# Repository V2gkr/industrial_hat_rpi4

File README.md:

HAT for Raspberry PI 4 with isolated rs232 , rs485 , CAN-FD

This board was made for personal use with other projects.
outputs for manufacturing:
1) gerbers and drill files
2) BOM for jlcpcb store
3) pick and place file

Board capabilities
1) isolated RS232 on standart UART pins (8 , 10)
2) isolated RS485 on additional UART with enable pin (27,28,29)
3) isolated CAN-FD on SPI0 (standard pins with interrupt pin on pin 15)

Production cost on jlcpcb for 5 prototypes is app. 150$

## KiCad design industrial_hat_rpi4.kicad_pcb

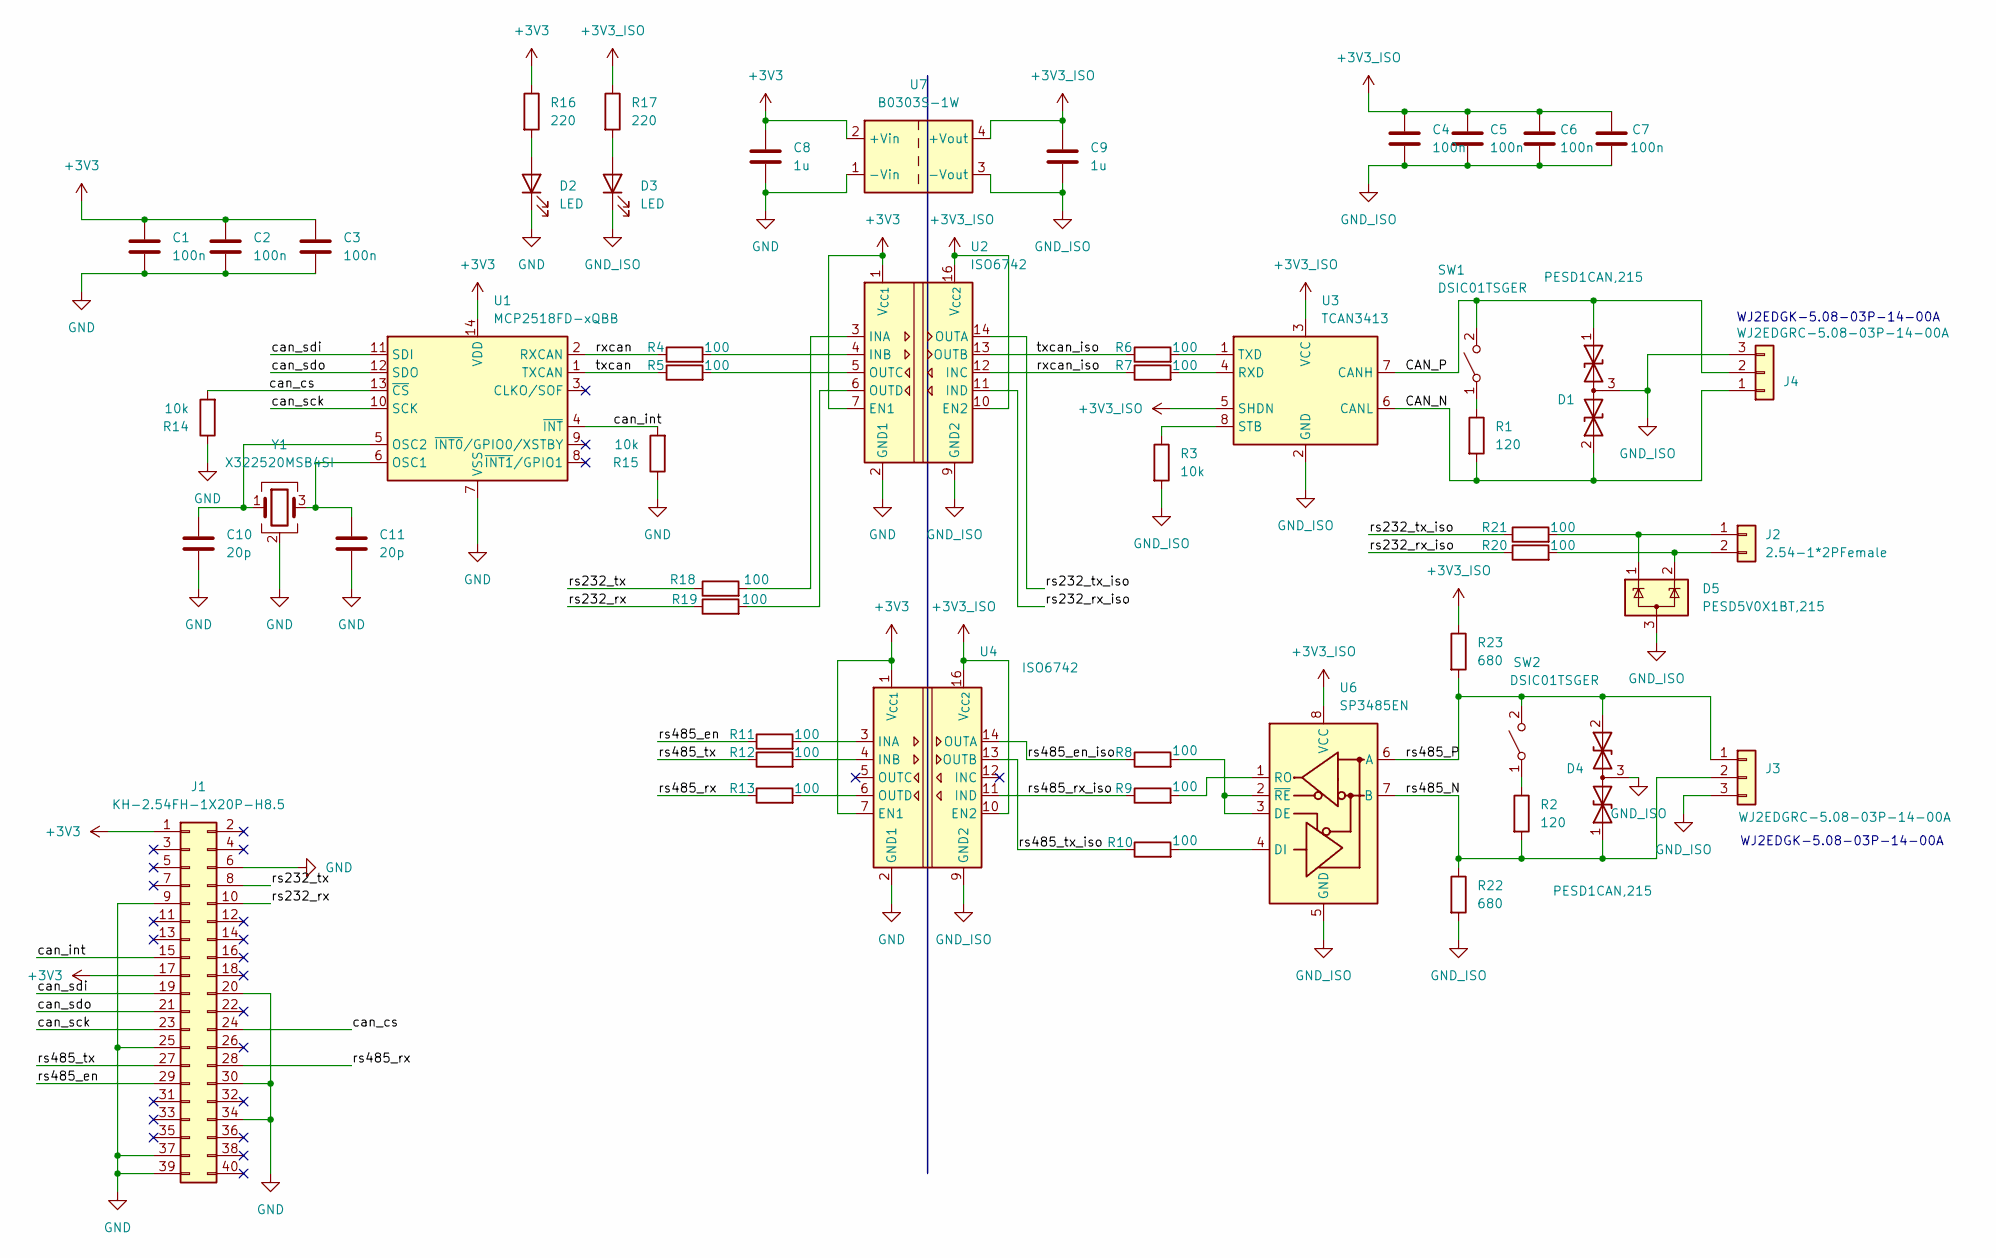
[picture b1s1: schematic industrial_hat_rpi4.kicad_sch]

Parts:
C1, C2, C3, C4, C5, C6, C7: 100n; C_0402_1005Metric; LCSC C60474
C8, C9: 1u; C_0603_1608Metric; LCSC C3905328
C10, C11: 20p; C_0402_1005Metric; LCSC C76959
D1, D4: PESD1CAN,215; SOT-23; LCSC C15771
D2, D3: LED; LED_0603_1608Metric; LCSC C99289
D5: PESD5V0X1BT,215; SOT-23-3; LCSC C456094
J1: KH-2.54FH-1X20P-H8.5; PinSocket_2x20_P2.54mm_Vertical_jlcbpcb_pnp_custom; LCSC C2905423
J2: 2.54-1*2PFemale; PinSocket_1x02_P2.54mm_Vertical_jlcpcb_pnp_custom; LCSC C49661
J3, J4: WJ2EDGRC-5.08-03P-14-00A; PhoenixContact_MSTBA_2,5_3-G-5,08_1x03_P5.08mm_Horizontal; LCSC C8377
R1, R2: 120; R_0603_1608Metric; LCSC C114681
R3, R14, R15: 10k; R_0603_1608Metric; LCSC C22369937
R4, R5, R6, R7, R8, R9, R10, R11, R12, R13, R18, R19, R20, R21: 100; R_0603_1608Metric; LCSC C163844
R16, R17: 220; R_0603_1608Metric; LCSC C384263
R22, R23: 680; R_0603_1608Metric; LCSC C25253
SW1, SW2: DSIC01TSGER; SW_DIP_SPSTx01_Slide_Copal_CHS-01B_W7.62mm_P1.27mm; LCSC C5145031
U1: MCP2518FD-xQBB; DFN-14-1EP_3x4.5mm_P0.65mm_EP1.65x4.25mm; LCSC C621395
U2, U4: ISO6742; SOIC-16W_7.5x10.3mm_P1.27mm; LCSC C5216407
U3: TCAN3413; SOIC-8_3.9x4.9mm_P1.27mm; LCSC C22433320
U6: SP3485EN; SOIC-8_3.9x4.9mm_P1.27mm; LCSC C22386564
U7: B0303S-1W; Converter_DCDC_Murata_CRE1xxxxxxSC_THT_jlcpcb_pnp_custom; LCSC C20622556
Y1: X322520MSB4SI; Crystal_SMD_3225-4Pin_3.2x2.5mm; LCSC C9004

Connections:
+3V3: C1.1, C2.1, C3.1, C8.1, J1.1, J1.17, R16.1, U1.14 (VDD), U2.1 (V_{CC1}), U2.7 (EN1), U4.1 (V_{CC1}), U4.7 (EN1), U7.2 (+Vin)
+3V3_ISO: C4.1, C5.1, C6.1, C7.1, C9.1, R17.1, R23.1, U2.10 (EN2), U2.16 (V_{CC2}), U3.3 (VCC), U3.5 (SHDN), U4.10 (EN2), U4.16 (V_{CC2}), U6.8 (VCC), U7.4 (+Vout)
/CAN_N: D1.2 (A2), J4.1, R1.2, U3.6 (CANL)
/CAN_P: D1.1 (A1), J4.2, SW1.2 (B), U3.7 (CANH)
/can_cs: J1.24, R14.2, U1.13 (~CS)
/can_int: J1.15, R15.2, U1.4 (~INT)
/can_sck: J1.23, U1.10 (SCK)
/can_sdi: J1.19, U1.11 (SDI)
/can_sdo: J1.21, U1.12 (SDO)
/rs232_rx: J1.10, R19.1
/rs232_rx_iso: R20.1, U2.11 (IND)
/rs232_tx: J1.8, R18.1
/rs232_tx_iso: R21.1, U2.14 (OUTA)
/rs485_N: D4.1 (A1), J3.2, R2.2, R22.1, U6.7 (B)
/rs485_P: D4.2 (A2), J3.1, R23.2, SW2.2 (B), U6.6 (A)
/rs485_en: J1.29, R11.1
/rs485_en_iso: R8.1, U4.14 (OUTA)
/rs485_rx: J1.28, R13.1
/rs485_rx_iso: R9.1, U4.11 (IND)
/rs485_tx: J1.27, R12.1
/rs485_tx_iso: R10.1, U4.13 (OUTB)
/rxcan: R4.1, U1.2 (RXCAN)
/rxcan_iso: R7.1, U2.12 (INC)
/txcan: R5.1, U1.1 (TXCAN)
/txcan_iso: R6.1, U2.13 (OUTB)
GND: C1.2, C2.2, C3.2, C8.2, C10.2, C11.2, D2.1 (K), J1.6, J1.9, J1.20, J1.25, J1.30, J1.34, J1.37, J1.39, R14.1, R15.1, U1.7 (VSS), U1.15 (VSS), U2.2 (GND1), U2.8 (GND1), U4.2 (GND1), U4.8 (GND1), U7.1 (-Vin), Y1.2 (G), Y1.4 (G)
GND_ISO: C4.2, C5.2, C6.2, C7.2, C9.2, D1.3 (common), D3.1 (K), D4.3 (common), D5.3 (A), J3.3, J4.3, R3.2, R22.2, U2.9 (GND2), U2.15 (GND2), U3.2 (GND), U4.9 (GND2), U4.15 (GND2), U6.5 (GND), U7.3 (-Vout)
unnamed: D2.2 (A), R16.2
unnamed: D3.2 (A), R17.2
unnamed: D5.1 (K), J2.1, R21.2
unnamed: D5.2 (K), J2.2, R20.2
unnamed: R1.1, SW1.1 (A)
unnamed: R2.1, SW2.1 (A)
unnamed: C11.1, U1.6 (OSC1), Y1.3
unnamed: C10.1, U1.5 (OSC2), Y1.1
unnamed: R18.2, U2.3 (INA)
unnamed: R4.2, U2.4 (INB)
unnamed: R5.2, U2.5 (OUTC)
unnamed: R19.2, U2.6 (OUTD)
unnamed: R7.2, U3.4 (RXD)
unnamed: R3.1, U3.8 (STB)
unnamed: R6.2, U3.1 (TXD)
unnamed: R11.2, U4.3 (INA)
unnamed: R12.2, U4.4 (INB)
unnamed: R13.2, U4.6 (OUTD)
unnamed: R8.2, U6.2 (~RE), U6.3 (DE)
unnamed: R10.2, U6.4 (DI)
unnamed: R9.2, U6.1 (RO)

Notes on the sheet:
WJ2EDGK-5.08-03P-14-00A

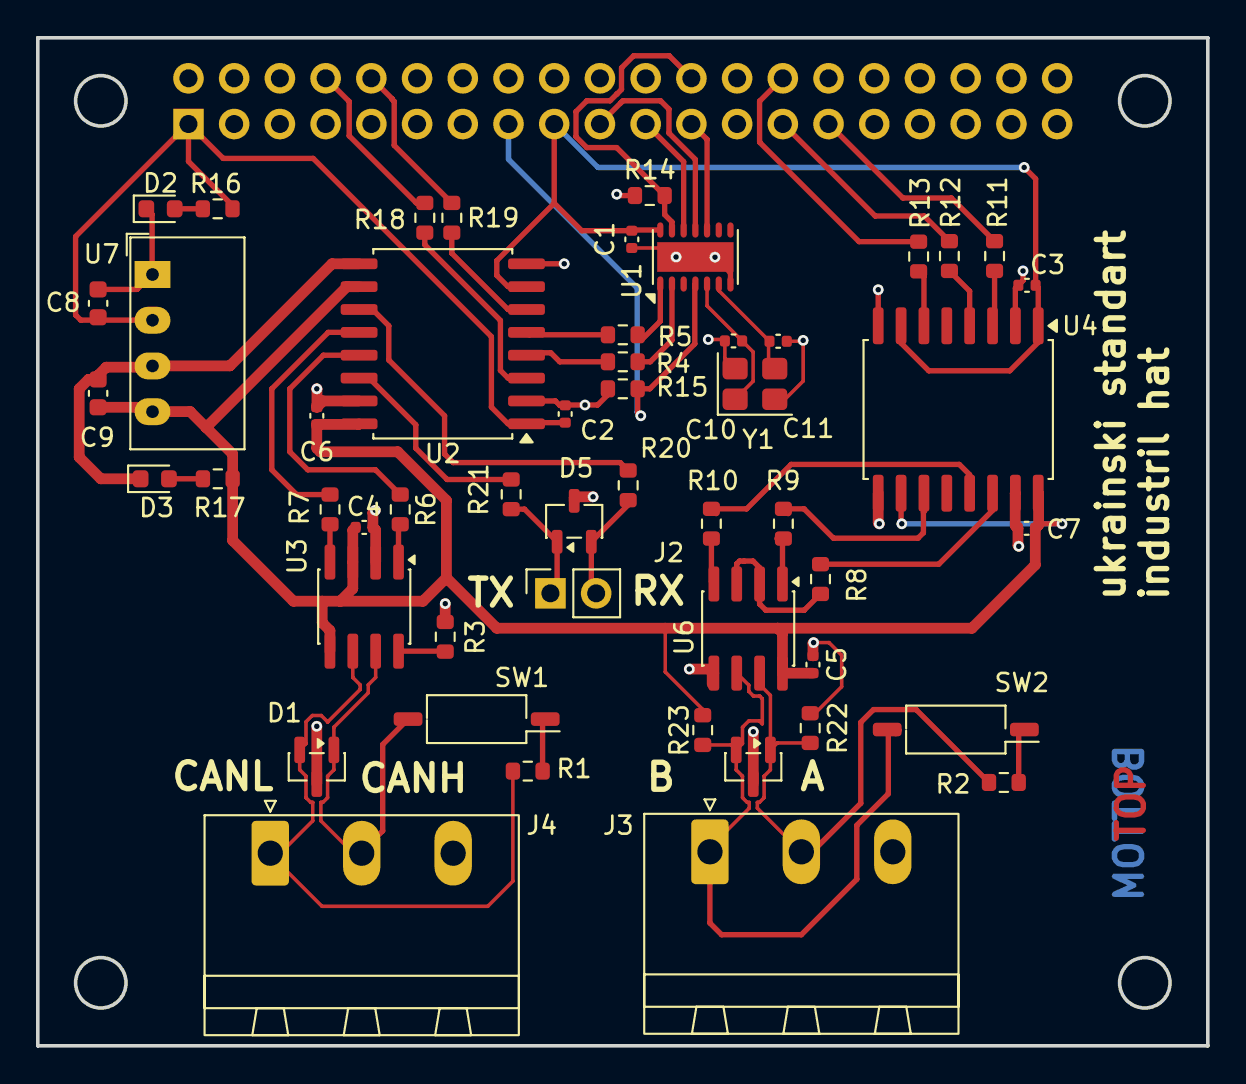
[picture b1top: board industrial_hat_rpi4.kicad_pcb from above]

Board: 2 copper layers, 65.0 x 56.0 mm, 52 parts (1 on the bottom side), 48 nets.

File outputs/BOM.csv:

"Reference","Value","Footprint","LCSC"
"C1,C2,C3,C4,C5,C6,C7","100n","Capacitor_SMD:C_0402_1005Metric","C60474"
"C8,C9","1u","Capacitor_SMD:C_0603_1608Metric","C3905328"
"C10,C11","20p","Capacitor_SMD:C_0402_1005Metric","C76959"
"D1,D4","PESD1CAN,215","Package_TO_SOT_SMD:SOT-23","C15771"
"D2,D3","LED","LED_SMD:LED_0603_1608Metric","C99289"
"D5","PESD5V0X1BT,215","Package_TO_SOT_SMD:SOT-23-3","C456094"
"J1","KH-2.54FH-1X20P-H8.5","Connector_PinSocket_2.54mm:PinSocket_2x20_P2.54mm_Vertical","C2905423"
"J2","2.54-1*2PFemale","Connector_PinSocket_2.54mm:PinSocket_1x02_P2.54mm_Vertical","C49661"
"J3,J4","WJ2EDGRC-5.08-03P-14-00A","Connector_Phoenix_GMSTB:PhoenixContact_GMSTBA_2,5_3-G-7,62_1x03_P7.62mm_Horizontal","C8377"
"R1,R2","120","Resistor_SMD:R_0603_1608Metric","C114681"
"R3,R14,R15","10k","Resistor_SMD:R_0603_1608Metric","C22369937"
"R4,R5,R6,R7,R8,R9,R10,R11,R12,R13,R18,R19,R20,R21","100","Resistor_SMD:R_0603_1608Metric","C163844"
"R16,R17","220","Resistor_SMD:R_0603_1608Metric","C384263"
"R22,R23","680","Resistor_SMD:R_0603_1608Metric","C25253"
"SW1,SW2","DSIC01TSGER","Button_Switch_SMD:SW_DIP_SPSTx01_Slide_Copal_CHS-01B_W7.62mm_P1.27mm","C5145031"
"U1","MCP2518FD-xQBB","Package_DFN_QFN:DFN-14-1EP_3x4.5mm_P0.65mm_EP1.65x4.25mm","C621395"
"U2,U4","ISO6742","Package_SO:SOIC-16W_7.5x10.3mm_P1.27mm","C5216407"
"U3","TCAN3413","Package_SO:SOIC-8_3.9x4.9mm_P1.27mm","C22433320"
"U6","SP3485EN","Package_SO:SOIC-8_3.9x4.9mm_P1.27mm","C22386564"
"U7","B0303S-1W","Converter_DCDC:Converter_DCDC_Murata_CRE1xxxxxxSC_THT","C20622556"
"Y1","X322520MSB4SI","Crystal:Crystal_SMD_3225-4Pin_3.2x2.5mm","C9004"

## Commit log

2026-06-22 added decoupling caps
2026-06-22 added differential line components
2026-06-23 changed isolators , assigned partnumbers
2026-06-23 schematic cleanup
2026-06-23 changed termination resistor switches
2026-06-23 added pcb
2026-06-23 assigned jlcpcb parts , pcb component placing inp
2026-06-23 component placement inp
2026-06-24 changed component placing and can , rs485 connectors
2026-06-25 changed can ,rs485 connections , routing in progress
2026-06-26 completed pcb
2026-06-26 added rs485 pull up down resistors, generated bom
2026-06-26 removed history directory
2026-06-26 removed jlcpcb folder
2026-06-26 changed silkscreen text placement
2026-06-26 modified gitignore
2026-06-26 updated switches footprints and layout
2026-06-26 added pick and place and bom in outputs folder
2026-06-26 added gerber and drill files
2026-06-26 added pick and place in csv
2026-06-26 updated output files
2026-06-27 final output files , small changes to footprints
